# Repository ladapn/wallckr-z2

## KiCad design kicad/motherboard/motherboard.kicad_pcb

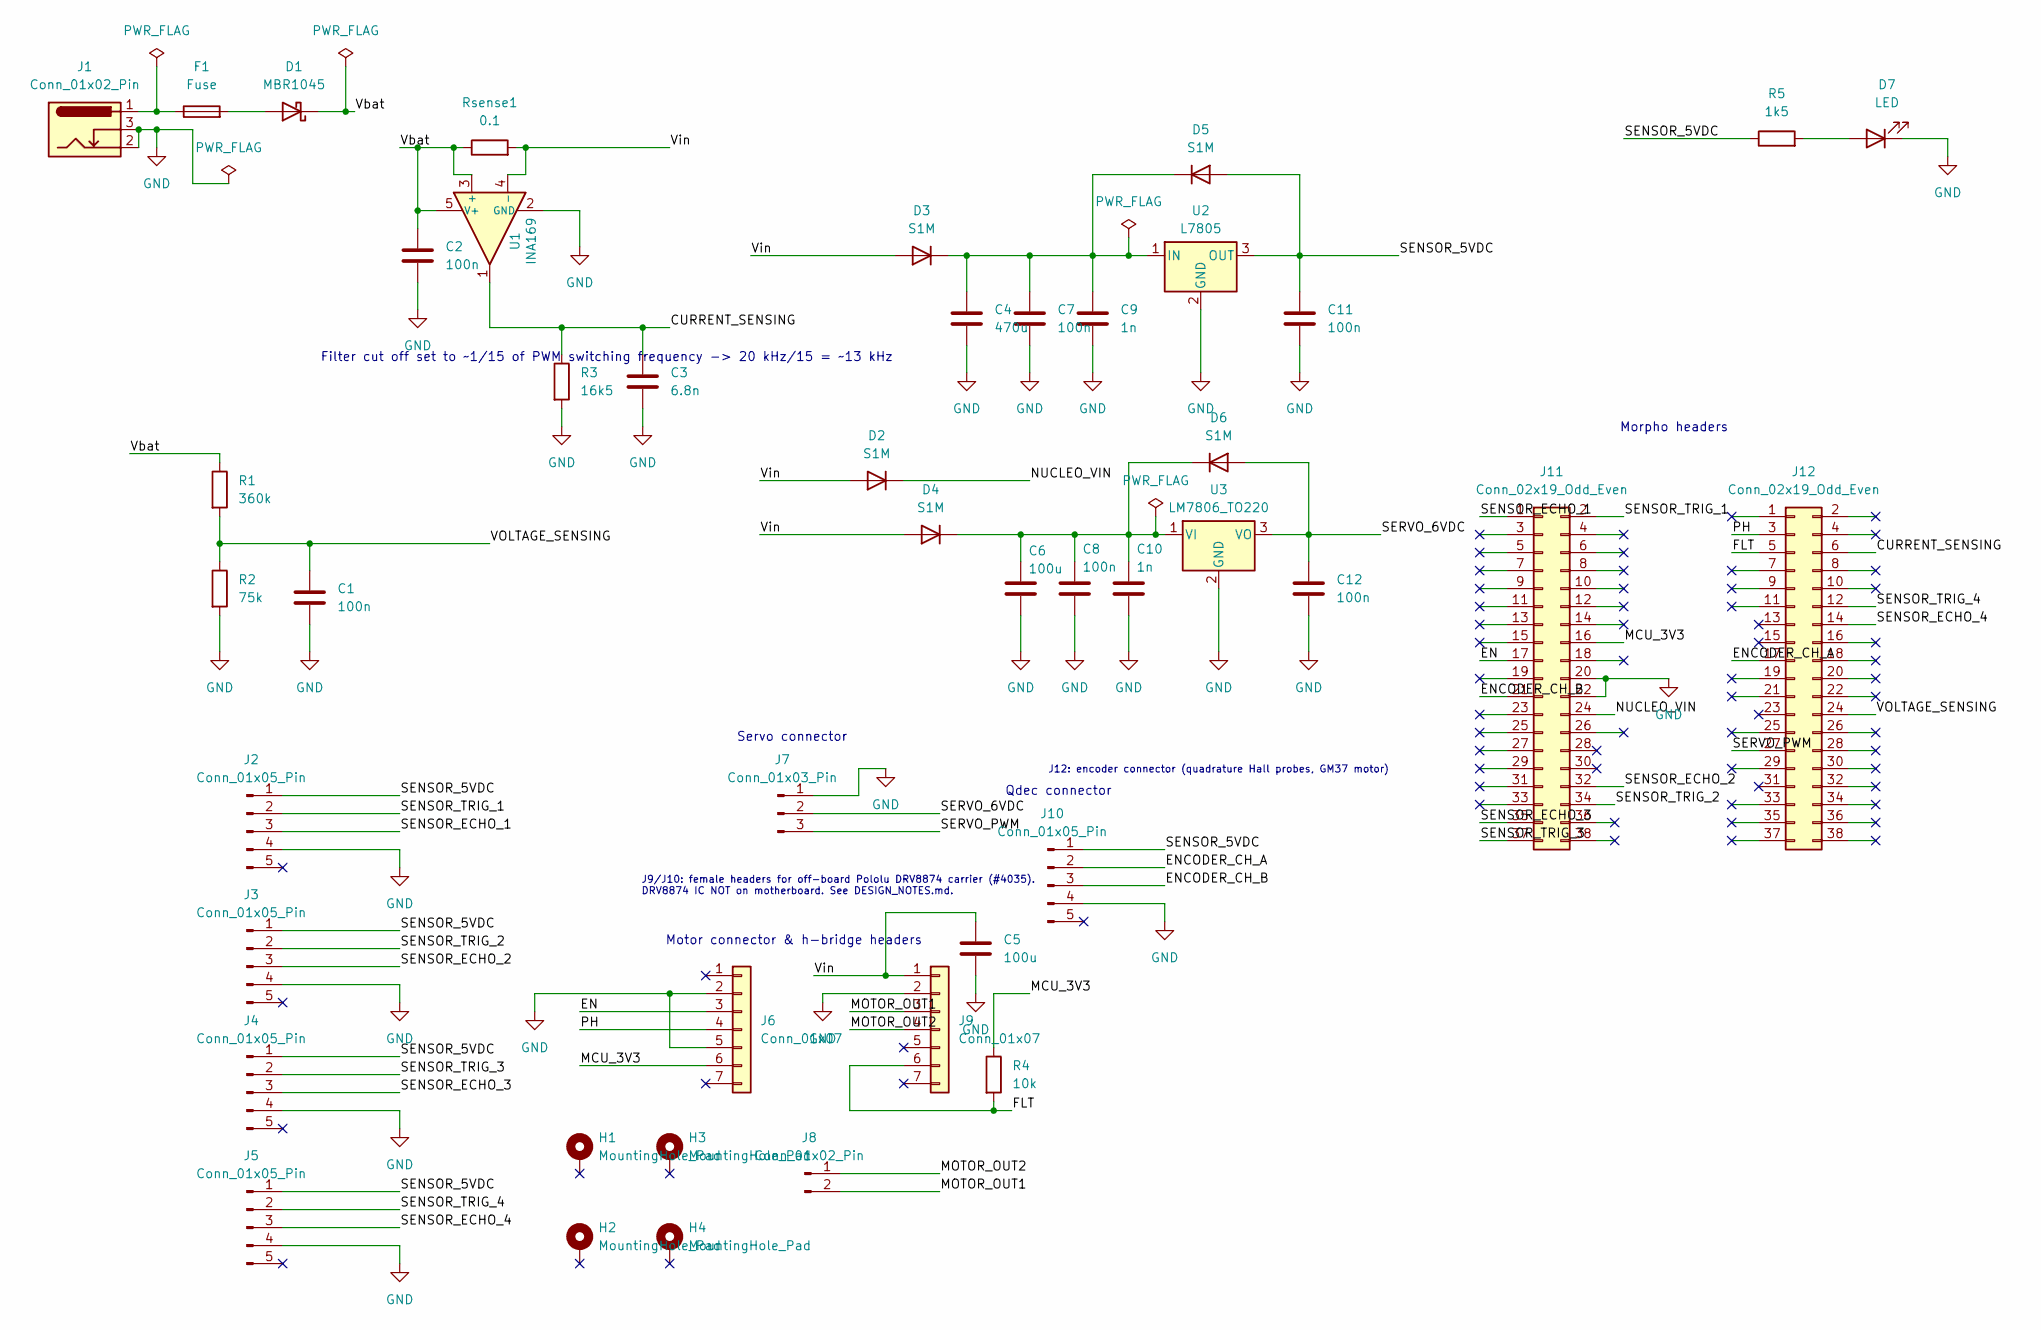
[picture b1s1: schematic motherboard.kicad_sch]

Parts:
C1, C2, C7, C8, C11, C12: 100n; C_0805_2012Metric_Pad1.18x1.45mm_HandSolder
C3: 6.8n; C_0805_2012Metric_Pad1.18x1.45mm_HandSolder
C4: 470u; CP_Radial_D10.0mm_P5.00mm
C5, C6: 100u; CP_Radial_D6.3mm_P2.50mm
C9, C10: 1n; C_0805_2012Metric_Pad1.18x1.45mm_HandSolder
D1: MBR1045; TO-220-2_Vertical
D2, D3, D4, D5, D6: S1M; D_SMA_Handsoldering
D7: LED; LED_D5.0mm
F1: Fuse; Fuseholder_Cylinder-5x20mm_Stelvio-Kontek_PTF78_Horizontal_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
H1, H2, H3, H4: MountingHole_Pad; MountingHole_3.7mm_Pad_TopBottom
J1: Conn_01x02_Pin; BarrelJack_Horizontal
J2, J3, J4, J5: Conn_01x05_Pin; Molex_KK-254_AE-6410-05A_1x05_P2.54mm_Vertical
J6, J9: Conn_01x07; PinSocket_1x07_P2.54mm_Vertical
J7: Conn_01x03_Pin; Molex_KK-254_AE-6410-03A_1x03_P2.54mm_Vertical
J8: Conn_01x02_Pin; Molex_KK-396_A-41792-0002_1x02_P3.96mm_Horizontal
J10: Conn_01x05_Pin; PinHeader_1x05_P2.54mm_Horizontal
J11, J12: Conn_02x19_Odd_Even; PinSocket_2x19_P2.54mm_Vertical_MirroredPins
R1: 360k; R_0805_2012Metric_Pad1.20x1.40mm_HandSolder
R2: 75k; R_0805_2012Metric_Pad1.20x1.40mm_HandSolder
R3: 16k5; R_0805_2012Metric_Pad1.20x1.40mm_HandSolder
R4: 10k; R_0805_2012Metric_Pad1.20x1.40mm_HandSolder
R5: 1k5; R_0805_2012Metric_Pad1.20x1.40mm_HandSolder
Rsense1: 0.1; R_Axial_DIN0922_L20.0mm_D9.0mm_P25.40mm_Horizontal
U1: INA169; SOT-23-5
U2: L7805; TO-220-3_Vertical
U3: LM7806_TO220; TO-220-3_Vertical

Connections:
/CURRENT_SENSING: C3.1, J12.6, R3.1, U1.1
/EN: J6.3, J11.17
/ENCODER_CH_A: J10.2, J12.17
/ENCODER_CH_B: J10.3, J11.21
/FLT: J9.6, J12.5, R4.2
/MCU_3V3: J6.6, J11.16, R4.1
/MOTOR_OUT1: J8.2, J9.3
/MOTOR_OUT2: J8.1, J9.4
/NUCLEO_VIN: D2.1 (K), J11.24
/PH: J6.4, J12.3
/SENSOR_5VDC: C11.1, D5.2 (A), J2.1, J3.1, J4.1, J5.1, J10.1, R5.1, U2.3 (OUT)
/SENSOR_ECHO_1: J2.3, J11.1
/SENSOR_ECHO_2: J3.3, J11.32
/SENSOR_ECHO_3: J4.3, J11.35
/SENSOR_ECHO_4: J5.3, J12.14
/SENSOR_TRIG_1: J2.2, J11.2
/SENSOR_TRIG_2: J3.2, J11.34
/SENSOR_TRIG_3: J4.2, J11.37
/SENSOR_TRIG_4: J5.2, J12.12
/SERVO_6VDC: C12.1, D6.2 (A), J7.2, U3.3 (VO)
/SERVO_PWM: J7.3, J12.27
/VOLTAGE_SENSING: C1.1, J12.24, R1.2, R2.1
/Vbat: C2.1, D1.1 (K), R1.1, Rsense1.1, U1.3 (+), U1.5 (V+)
/Vin: C5.1, D2.2 (A), D3.2 (A), D4.2 (A), J9.1, Rsense1.2, U1.4 (-)
GND: C1.2, C2.2, C3.2, C4.2, C5.2, C6.2, C7.2, C8.2, C9.2, C10.2, C11.2, C12.2, D7.1 (K), J1.2, J1.3, J2.4, J3.4, J4.4, J5.4, J6.2, J6.5, J7.1, J9.2, J10.4, J11.20, J11.22, R2.2, R3.2, U1.2 (GND), U2.2 (GND), U3.2 (GND)
unnamed: D1.2 (A), F1.2
unnamed: C4.1, C7.1, C9.1, D3.1 (K), D5.1 (K), U2.1 (IN)
unnamed: C6.1, C8.1, C10.1, D4.1 (K), D6.1 (K), U3.1 (VI)
unnamed: D7.2 (A), R5.2
unnamed: F1.1, J1.1

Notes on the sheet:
Filter cut off set to ~1/15 of PWM switching frequency -> 20 kHz/15 = ~13 kHz
J12: encoder connector (quadrature Hall probes, GM37 motor)
Servo connector
J9/J10: female headers for off-board Pololu DRV8874 carrier (#4035). DRV8874 IC NOT on motherboard. See DESIGN_NOTES.md.
Qdec connector
Morpho headers
Motor connector & h-bridge headers

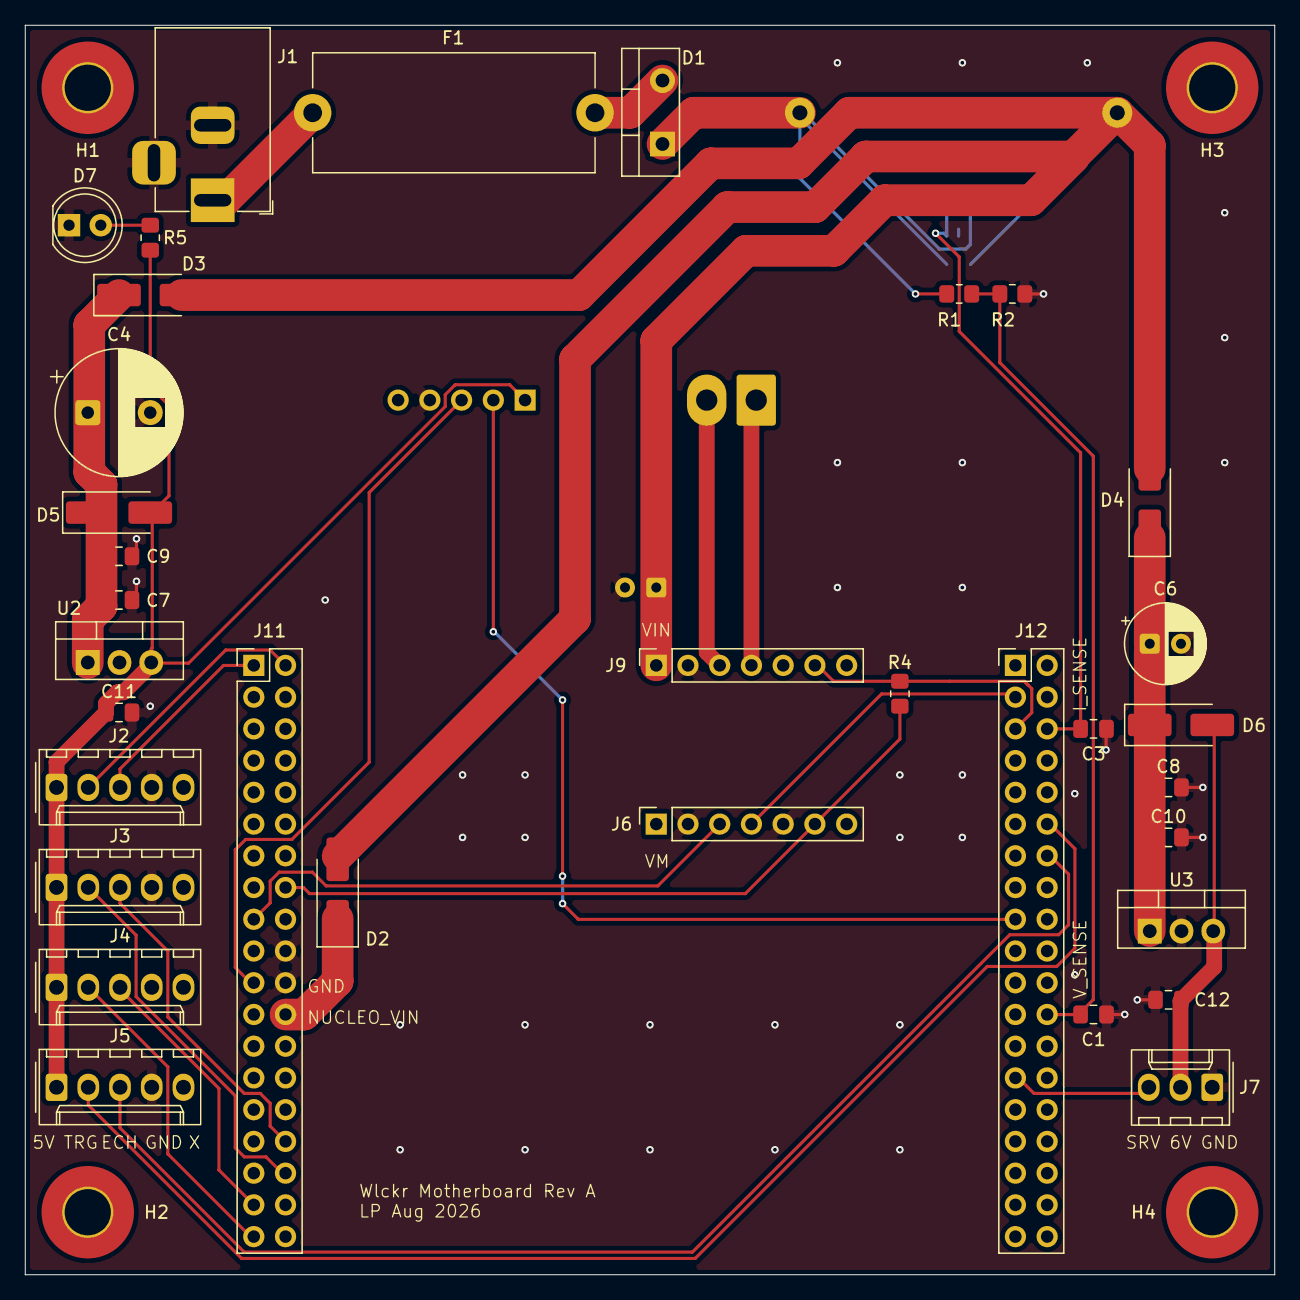
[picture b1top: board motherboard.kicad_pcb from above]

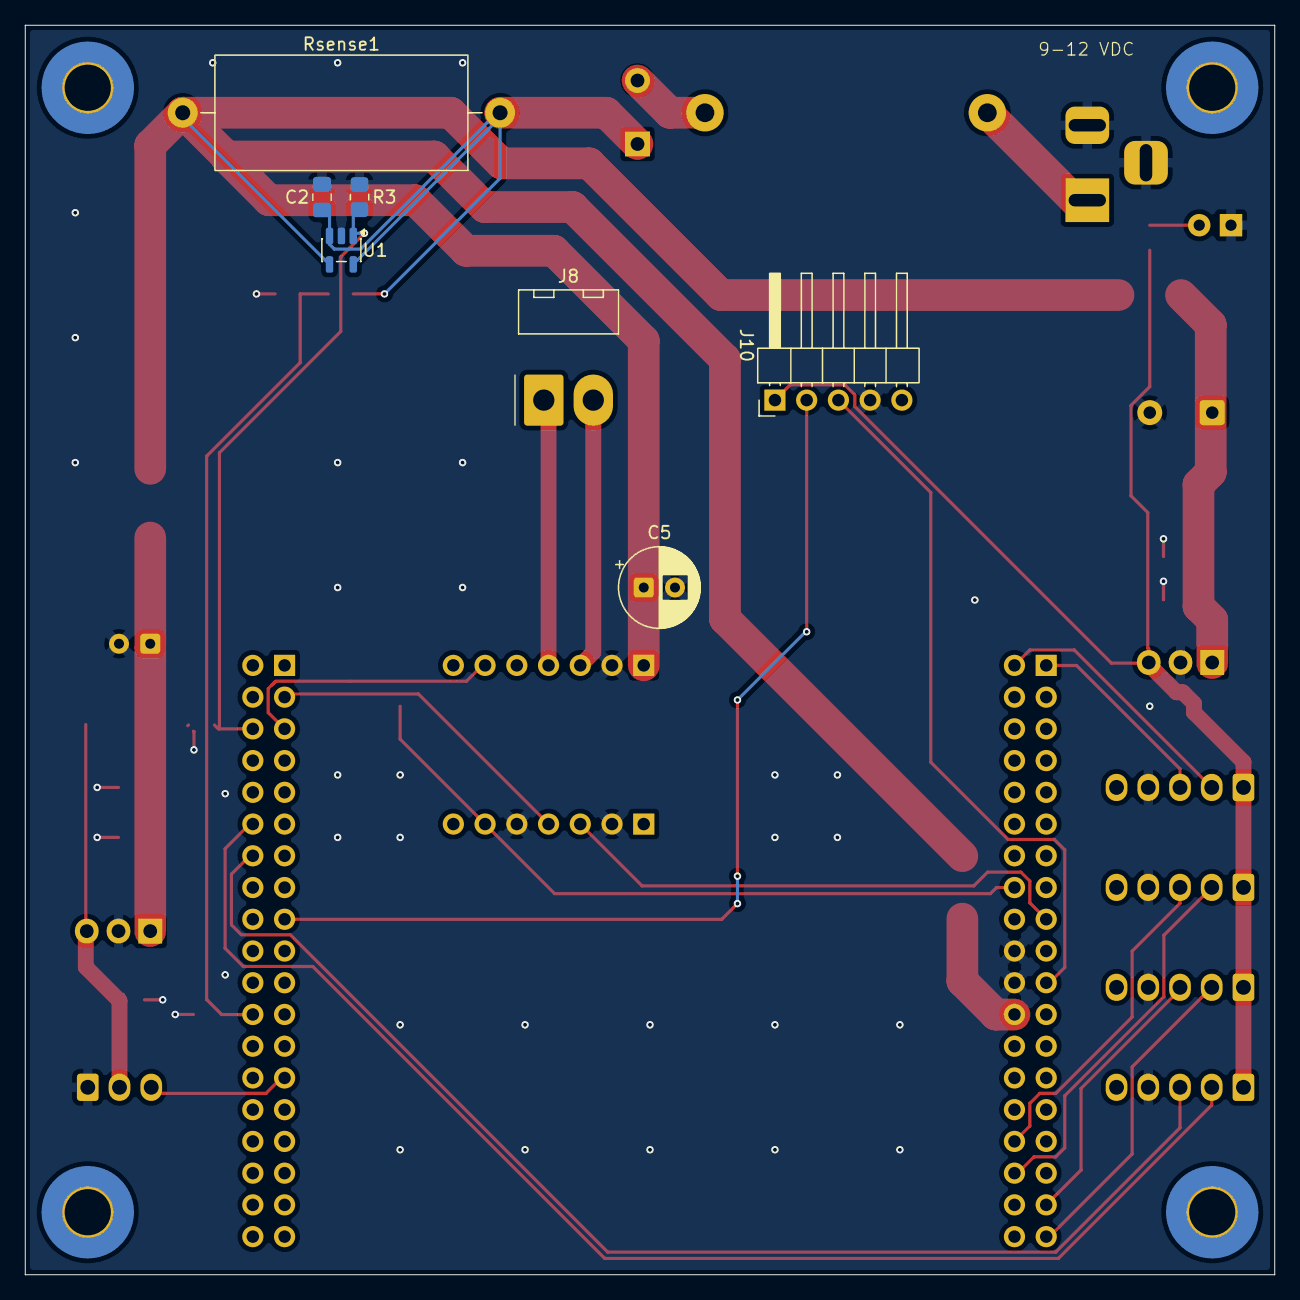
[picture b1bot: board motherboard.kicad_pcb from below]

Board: 2 copper layers, 100.0 x 100.0 mm, 45 parts (7 on the bottom side), 30 nets.
